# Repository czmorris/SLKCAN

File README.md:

# SLKCAN
SLKCAN (Slick CAN) PCB. 

This board was created as project to connect to the CANBus on a City Slicker electric motorcycle (Though it may work with other canbus devices).

Goal:
- Programmable via the Arduino IDE (Uses an ESP32). This allows anyone who uses it to customize it to their own needs.
- Connect to the CANBus on the motorcycle. (Uses MCP2551 and MCP2515, Noise management was also required)
- Provide a means to get 3.3 and 5v power from the 12v supply on the bikes data port.
- Provide a means to get this information out via serial. Or to be reprogrammed via serial. Pin header provided.
- Provide a header with some additional GPIO.

note: I use an FTDI cable for programming and getting serial terminal information.
I have also tested with cheaper USB TTL modules with no issues. Other adapters may work as well.

At this time this device does not promise to be foolproof. Connect this to your bike at your own risk.

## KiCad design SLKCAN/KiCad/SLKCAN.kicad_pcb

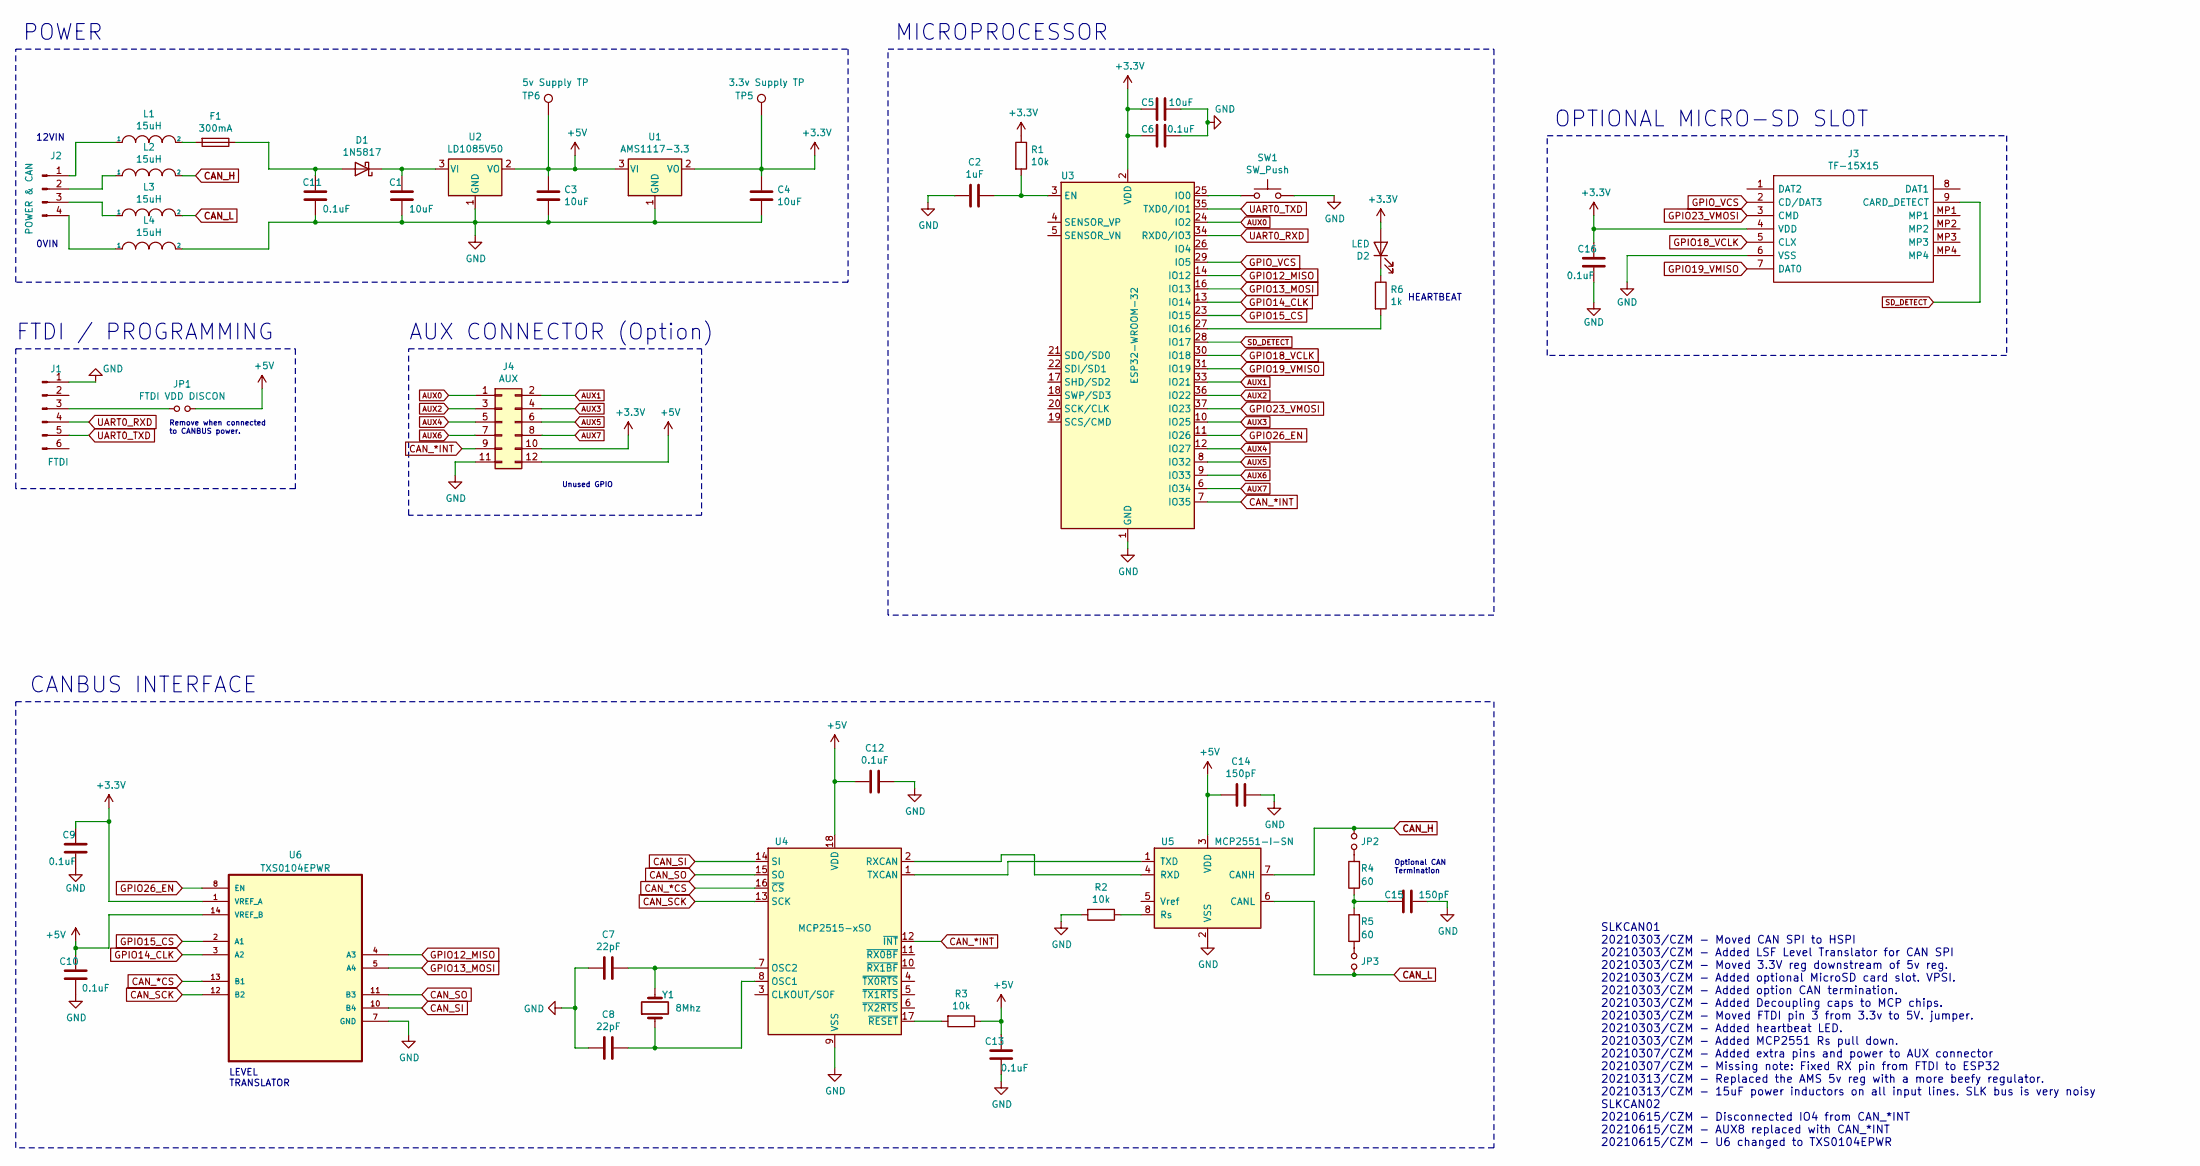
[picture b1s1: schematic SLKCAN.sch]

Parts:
C1, C3, C4, C5: 10uF; C_0805_2012Metric
C2: 1uF; C_0805_2012Metric
C6, C9, C10, C11, C12, C13, C16: 0.1uF; C_0805_2012Metric
C7, C8: 22pF; C_0805_2012Metric
C14, C15: 150pF; C_0805_2012Metric
D1: 1N5817; D_SOD-123
D2: LED; LED_0805_2012Metric
F1: 300mA; Fuse_0603_1608Metric
J1: FTDI; PinHeader_1x06_P2.54mm_Vertical
J2: POWER & CAN; PinHeader_1x04_P2.54mm_Horizontal
J3: TF-15X15; TF15X15; Manufacturer_Part_Number TF-15X15
J4: AUX; PinHeader_2x06_P2.54mm_Vertical
JP1: FTDI VDD DISCON; PinHeader_1x02_P2.54mm_Vertical
JP2, JP3: Jumper_NO_Small; SolderJumper-2_P1.3mm_Open_RoundedPad1.0x1.5mm
L1, L2, L3, L4: 15uH; SUNLORD_SWPA5020S_CZM
R1, R2, R3: 10k; R_0805_2012Metric
R4, R5: 60; R_0805_2012Metric
R6: 1k; R_0805_2012Metric
SW1: SW_Push; SW_SPST_CK_RS282G05A3
TP5: 3.3v Supply TP; TestPoint_Pad_D1.0mm
TP6: 5v Supply TP; TestPoint_Pad_D1.0mm
U1: AMS1117-3.3; SOT-223-3_TabPin2
U2: LD1085V50; TO-220-3_Horizontal_TabDown
U3: ESP32-WROOM-32
U4: MCP2515-xSO; SOIC-18W_7.5x11.6mm_P1.27mm
U5: MCP2551-I-SN; SOIC-8_3.9x4.9mm_P1.27mm
U6: TXS0104EPWR; SOP65P640X120-14N
Y1: 8Mhz; Crystal_SMD_5032-2Pin_5.0x3.2mm

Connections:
+3V3: C4.1, C5.2, C6.2, C9.2, C16.2, D2.2 (A), J3.4 (VDD), J4.10, R1.1, TP5.1, U1.2 (VO), U3.2 (VDD), U6.1 (VREF_A)
+5V: C3.1, C10.2, C12.2, C13.2, C14.2, J4.12, JP1.2, R3.1, TP6.1, U1.3 (VI), U2.2 (VO), U4.18 (VDD), U5.3 (VDD), U6.14 (VREF_B)
AUX0: J4.1, U3.24 (IO2)
AUX1: J4.2, U3.33 (IO21)
AUX2: J4.3, U3.36 (IO22)
AUX3: J4.4, U3.10 (IO25)
AUX4: J4.5, U3.12 (IO27)
AUX5: J4.6, U3.8 (IO32)
AUX6: J4.7, U3.9 (IO33)
AUX7: J4.8, U3.6 (IO34)
CAN_*CS: U4.16 (~CS), U6.13 (B1)
CAN_*INT: J4.9, U3.7 (IO35), U4.12 (~INT)
CAN_H: JP2.1, L2.2, U5.7 (CANH)
CAN_L: JP3.2, L3.2, U5.6 (CANL)
CAN_SCK: U4.13 (SCK), U6.12 (B2)
CAN_SI: U4.14 (SI), U6.10 (B4)
CAN_SO: U4.15 (SO), U6.11 (B3)
GND: C1.2, C2.2, C3.2, C4.2, C5.1, C6.1, C7.2, C8.2, C9.1, C10.1, C11.2, C12.1, C13.1, C14.1, C15.2, C16.1, J1.1, J3.6 (VSS), J4.11, L4.2, R2.2, SW1.2, U1.1 (GND), U2.1 (GND), U3.1 (GND), U3.15 (GND), U3.38 (GND), U3.39 (GND), U4.9 (VSS), U5.2 (VSS), U6.7 (GND)
GPIO12_MISO: U3.14 (IO12), U6.4 (A3)
GPIO13_MOSI: U3.16 (IO13), U6.5 (A4)
GPIO14_CLK: U3.13 (IO14), U6.3 (A2)
GPIO15_CS: U3.23 (IO15), U6.2 (A1)
GPIO18_VCLK: J3.5 (CLX), U3.30 (IO18)
GPIO19_VMISO: J3.7 (DAT0), U3.31 (IO19)
GPIO23_VMOSI: J3.3 (CMD), U3.37 (IO23)
GPIO26_EN: U3.11 (IO26), U6.8 (EN)
GPIO_VCS: J3.2 (CD/DAT3), U3.29 (IO5)
unnamed: C1.1, D1.1 (K), U2.3 (VI)
unnamed: C2.1, R1.2, U3.3 (EN)
unnamed: C7.1, U4.7 (OSC2), Y1.2
unnamed: C8.1, U4.8 (OSC1), Y1.1
unnamed: C11.1, D1.2 (A), F1.1
unnamed: C15.1, R4.1, R5.2
unnamed: D2.1 (K), R6.1
unnamed: F1.2, L1.2
unnamed: J1.3, JP1.1
unnamed: J2.1, L1.1
unnamed: J2.2, L2.1
unnamed: J2.3, L3.1
unnamed: J2.4, L4.1
unnamed: JP2.2, R4.2
unnamed: JP3.1, R5.1
unnamed: R2.1, U5.8 (Rs)
unnamed: R3.2, U4.17 (~RESET)
unnamed: R6.2, U3.27 (IO16)
unnamed: SW1.1, U3.25 (IO0)
unnamed: U4.1 (TXCAN), U5.1 (TXD)
unnamed: U4.2 (RXCAN), U5.4 (RXD)
SD_DETECT: J3.9 (CARD_DETECT), U3.28 (IO17)
UART0_RXD: J1.4, U3.34 (RXD0/IO3)
UART0_TXD: J1.5, U3.35 (TXD0/IO1)

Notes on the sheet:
LEVEL TRANSLATOR
12VIN
0VIN
HEARTBEAT
POWER
FTDI / PROGRAMMING
MICROPROCESSOR
OPTIONAL MICRO-SD SLOT
CANBUS INTERFACE
SLKCAN01 20210303/CZM - Moved CAN SPI to HSPI 20210303/CZM - Added LSF Level Translator for CAN SPI 20210303/CZM - Moved 3.3V reg downstream of 5v reg. 20210303/CZM - Added optional MicroSD card slot. VPSI. 20210303/CZM - Added option CAN termination. 20210303/CZM - Added Decoupling caps to MCP chi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
Optional CAN Termination
AUX CONNECTOR (Option)
Remove when connected to CANBUS power.
Unused GPIO

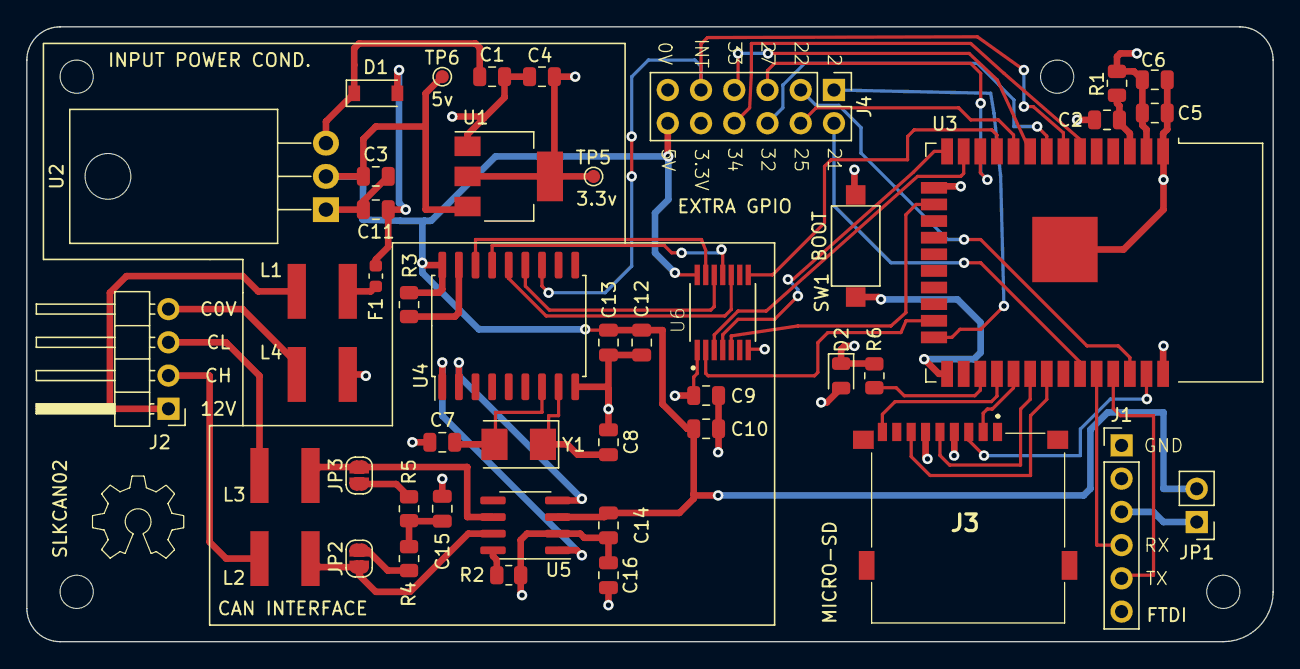
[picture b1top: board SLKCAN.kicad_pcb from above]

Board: 4 copper layers, 95.3 x 47.0 mm, 46 parts (0 on the bottom side), 51 nets.

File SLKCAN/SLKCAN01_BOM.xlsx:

Comment | Designator | Footprint | LCSC Part #（optional）
15uH Ind | L1, L2, L3, L4 | SWPA5020 | C55435
Fuse | F1 | 603.0 | C207010
5vREG | U2 | TO-220 | C283283
3.3REG | U1 | SOT-223 | C6186
ESP | U3 | QFN-38 | C82899
SD | J3 | 14.5x14.75X1.85mm | C111196
LVL IC | U6 | TSSOP-14 | C202288
MCP | U4 | SOIC-18 | C12368
MCP | U5 | SOIC-8 | C49558
XTAL | Y1 | SMD-5032 | C115962
DIODE | D1 | SOD-123 | C727113
LED | D2 | LED_0805 | C84256
.1uF | C6, C9-13, C16 | 805.0 | C696367
10uF | C1, C3-5 | 805.0 | C15850
1uF | C2 | 805.0 | C28323
22pF | C7, C8 | 805.0 | C1804
150pF | C14, C15 | 805.0 | C1716
10K | R1-3 | 805.0 | C17414
1K | R6 | 805.0 | C17513
60.0 | R4-5 | 805.0 | C72998
BTN | SW1 | SW-SMD-3.6X6.1 | C118141

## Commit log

2021-04-14 Added Rework notes schematic
    Added rework notes in RED to the schematic pdf file. Rework notes represent the changes that needed to be made to the board after production.
2021-04-18 Added cables drawing
2021-04-18 Update SLK_CABLES_DRAWING.pdf
    Corrected RX/TX on drawing.
2021-06-15 Fixes from SLKCAN01 known issues
    Fixes from SLKCAN01 known issues.
2021-06-15 Removed old gerbers, pdfs, and renders
    Removed old gerbers, pdfs, and renders
2021-06-15 New gerbers, rendres, and schematic pdf.
    New gerbers, rendres, and schematic pdf.
    Note: At this time I have not ordered and tested this revision. If you decide to order some use caution.
